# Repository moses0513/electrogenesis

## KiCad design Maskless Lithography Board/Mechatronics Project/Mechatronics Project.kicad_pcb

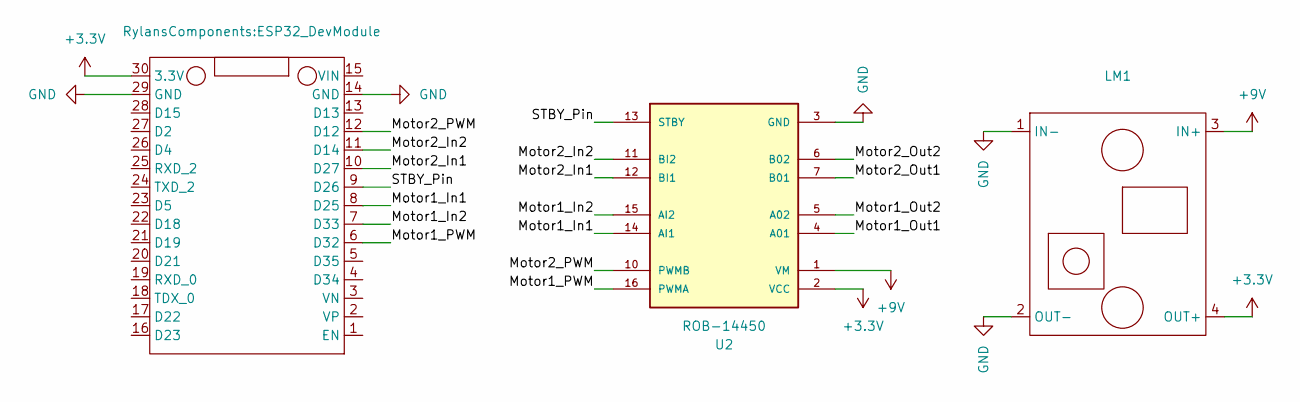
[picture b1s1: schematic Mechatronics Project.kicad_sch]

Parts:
ESP32_DevModule1: ESP32_DevModule
LM1: DC-DC LM2596
U2: ROB-14450; MODULE_ROB-14450; PARTREV 11-13-17

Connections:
+3.3V: ESP32_DevModule1.30 (3.3V), LM1.4 (OUT+), U2.2 (VCC)
+9V: LM1.3 (IN+), U2.1 (VM)
/Motor1_In1: ESP32_DevModule1.8 (D25), U2.14 (AI1)
/Motor1_In2: ESP32_DevModule1.7 (D33), U2.15 (AI2)
/Motor1_Out1: U2.4 (A01)
/Motor1_Out2: U2.5 (A02)
/Motor1_PWM: ESP32_DevModule1.6 (D32), U2.16 (PWMA)
/Motor2_In1: ESP32_DevModule1.10 (D27), U2.12 (BI1)
/Motor2_In2: ESP32_DevModule1.11 (D14), U2.11 (BI2)
/Motor2_Out1: U2.7 (B01)
/Motor2_Out2: U2.6 (B02)
/Motor2_PWM: ESP32_DevModule1.12 (D12), U2.10 (PWMB)
/STBY_Pin: ESP32_DevModule1.9 (D26), U2.13 (STBY)
GND: ESP32_DevModule1.14 (GND), ESP32_DevModule1.29 (GND), LM1.1 (IN-), LM1.2 (OUT-), U2.3 (GND), U2.8 (GND), U2.9 (GND)

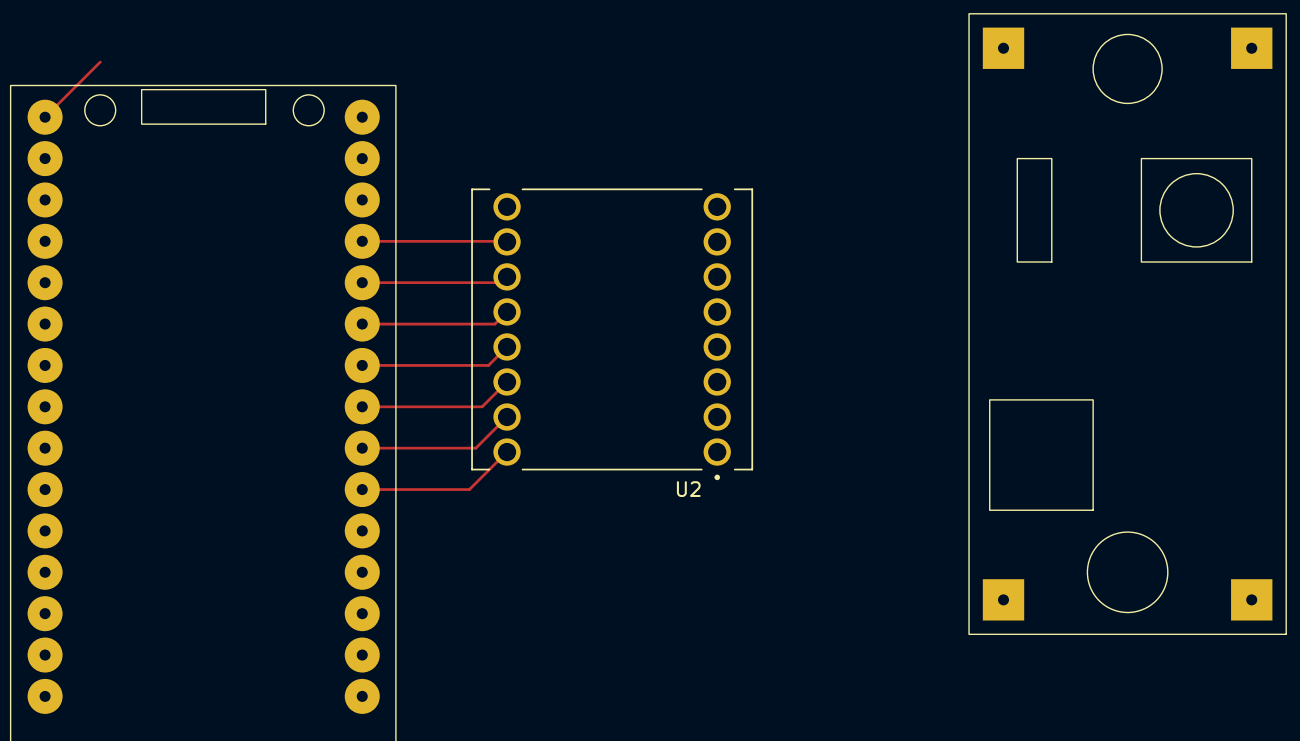
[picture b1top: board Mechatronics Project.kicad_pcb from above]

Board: 2 copper layers, 3 parts (0 on the bottom side), 10 nets.

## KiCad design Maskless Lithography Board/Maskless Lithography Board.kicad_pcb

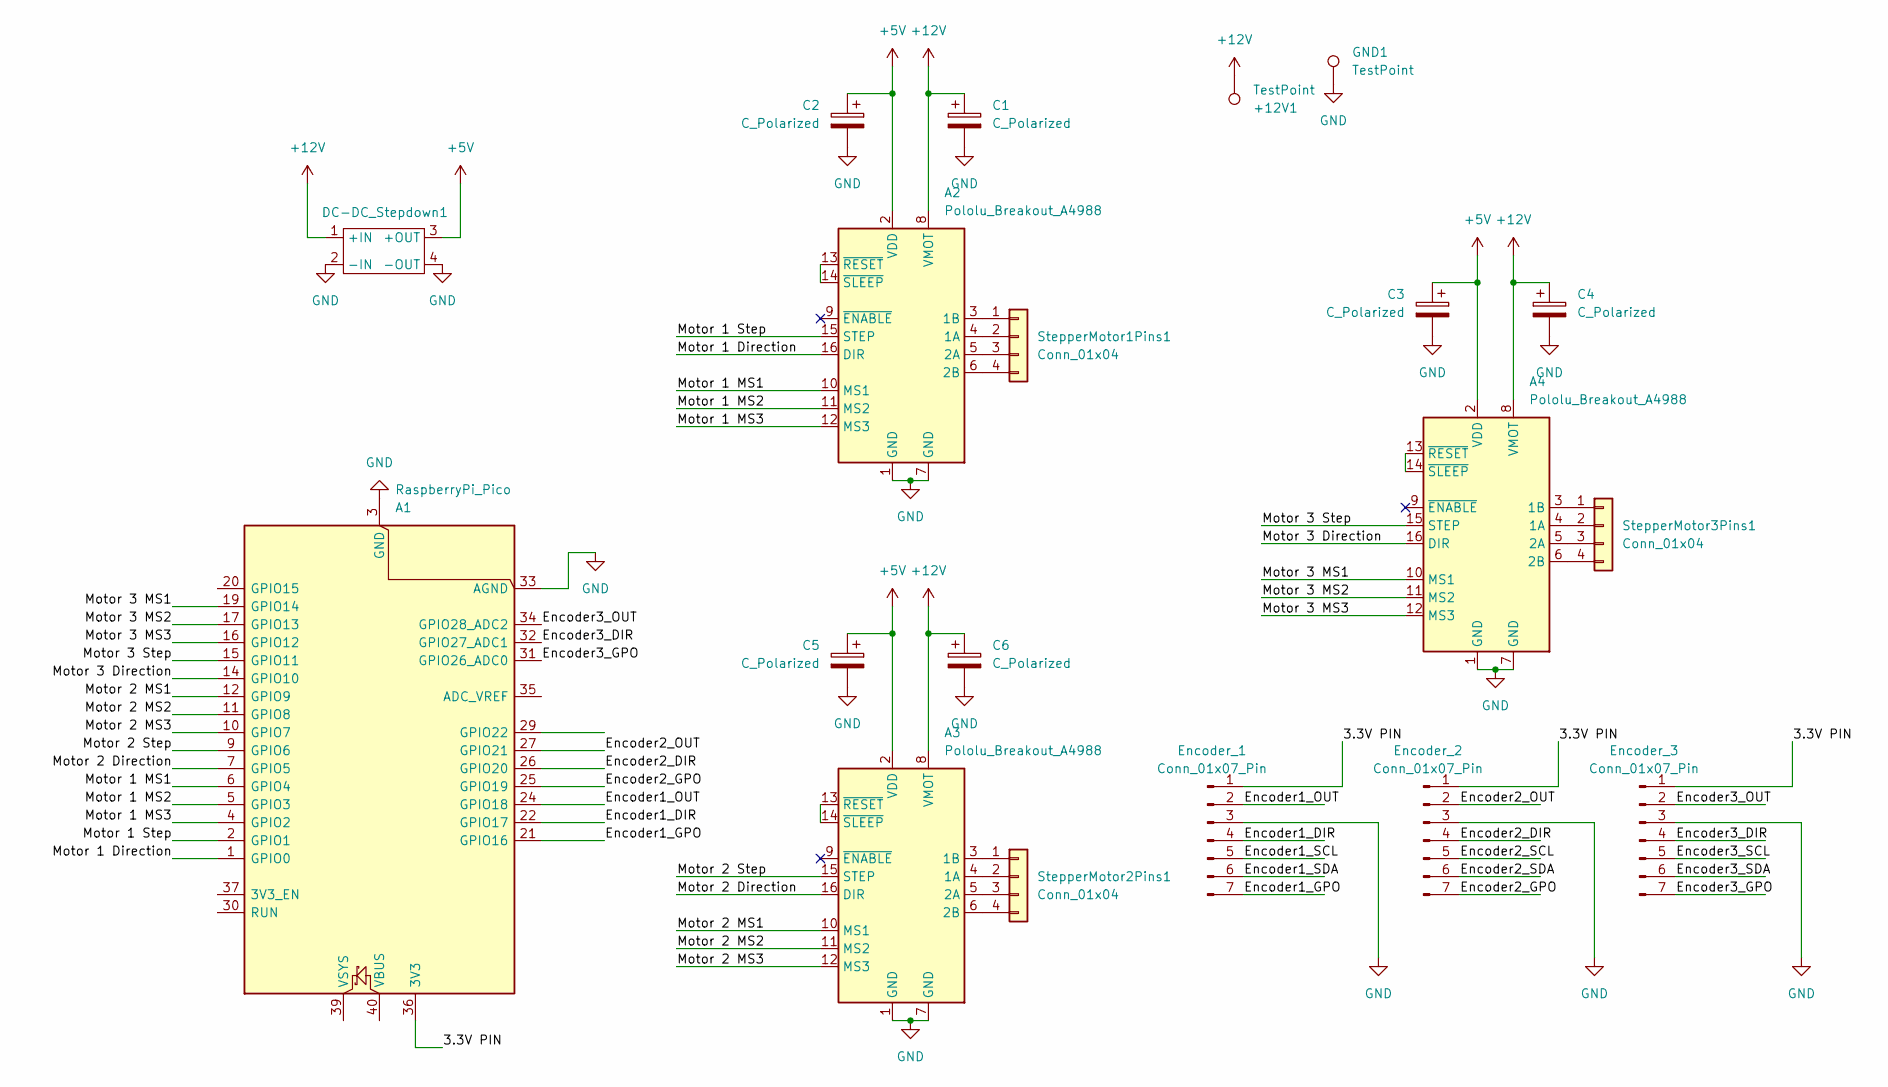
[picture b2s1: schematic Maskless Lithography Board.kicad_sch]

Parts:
+12V1: TestPoint; TestPoint_THTPad_D3.0mm_Drill1.5mm
A1: RaspberryPi_Pico; RaspberryPi_Pico_Common_Unspecified
A2, A3, A4: Pololu_Breakout_A4988; Pololu_Breakout-16_15.2x20.3mm
C1, C4, C6: C_Polarized; CP_Radial_D5.0mm_P2.50mm
C2, C3, C5: C_Polarized; C_Disc_D3.0mm_W1.6mm_P2.50mm
DC-DC_Stepdown1: Mini360_DC-DC_Stepdown
Encoder_1, Encoder_2, Encoder_3: Conn_01x07_Pin; JST_EH_B7B-EH-A_1x07_P2.50mm_Vertical
GND1: TestPoint; TestPoint_THTPad_3.0x3.0mm_Drill1.5mm
StepperMotor1Pins1, StepperMotor2Pins1, StepperMotor3Pins1: Conn_01x04; PinHeader_1x04_P2.54mm_Vertical

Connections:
+5V: A2.2 (VDD), A3.2 (VDD), A4.2 (VDD), C2.1, C3.1, C5.1, DC-DC_Stepdown1.3 (+OUT)
+12V: +12V1.1, A2.8 (VMOT), A3.8 (VMOT), A4.8 (VMOT), C1.1, C4.1, C6.1, DC-DC_Stepdown1.1 (+IN)
/3.3V PIN: A1.36 (3V3), Encoder_1.1, Encoder_2.1, Encoder_3.1
/Encoder1_DIR: A1.22 (GPIO17), Encoder_1.4
/Encoder1_GPO: A1.21 (GPIO16), Encoder_1.7
/Encoder1_OUT: A1.24 (GPIO18), Encoder_1.2
/Encoder1_SCL: Encoder_1.5
/Encoder1_SDA: Encoder_1.6
/Encoder2_DIR: A1.26 (GPIO20), Encoder_2.4
/Encoder2_GPO: A1.25 (GPIO19), Encoder_2.7
/Encoder2_OUT: A1.27 (GPIO21), Encoder_2.2
/Encoder2_SCL: Encoder_2.5
/Encoder2_SDA: Encoder_2.6
/Encoder3_DIR: A1.32 (GPIO27_ADC1), Encoder_3.4
/Encoder3_GPO: A1.31 (GPIO26_ADC0), Encoder_3.7
/Encoder3_OUT: A1.34 (GPIO28_ADC2), Encoder_3.2
/Encoder3_SCL: Encoder_3.5
/Encoder3_SDA: Encoder_3.6
/Motor 1 Direction: A1.1 (GPIO0), A2.16 (DIR)
/Motor 1 MS1: A1.6 (GPIO4), A2.10 (MS1)
/Motor 1 MS2: A1.5 (GPIO3), A2.11 (MS2)
/Motor 1 MS3: A1.4 (GPIO2), A2.12 (MS3)
/Motor 1 Step: A1.2 (GPIO1), A2.15 (STEP)
/Motor 2 Direction: A1.7 (GPIO5), A3.16 (DIR)
/Motor 2 MS1: A1.12 (GPIO9), A3.10 (MS1)
/Motor 2 MS2: A1.11 (GPIO8), A3.11 (MS2)
/Motor 2 MS3: A1.10 (GPIO7), A3.12 (MS3)
/Motor 2 Step: A1.9 (GPIO6), A3.15 (STEP)
/Motor 3 Direction: A1.14 (GPIO10), A4.16 (DIR)
/Motor 3 MS1: A1.19 (GPIO14), A4.10 (MS1)
/Motor 3 MS2: A1.17 (GPIO13), A4.11 (MS2)
/Motor 3 MS3: A1.16 (GPIO12), A4.12 (MS3)
/Motor 3 Step: A1.15 (GPIO11), A4.15 (STEP)
GND: A1.3 (GND), A1.8 (GND), A1.13 (GND), A1.18 (GND), A1.23 (GND), A1.28 (GND), A1.33 (AGND), A1.38 (GND), A2.1 (GND), A2.7 (GND), A3.1 (GND), A3.7 (GND), A4.1 (GND), A4.7 (GND), C1.2, C2.2, C3.2, C4.2, C5.2, C6.2, DC-DC_Stepdown1.2 (-IN), DC-DC_Stepdown1.4 (-OUT), Encoder_1.3, Encoder_2.3, Encoder_3.3, GND1.1
unnamed: A2.4 (1A), StepperMotor1Pins1.2
unnamed: A2.3 (1B), StepperMotor1Pins1.1
unnamed: A2.5 (2A), StepperMotor1Pins1.3
unnamed: A2.6 (2B), StepperMotor1Pins1.4
unnamed: A2.13 (~RESET), A2.14 (~SLEEP)
unnamed: A3.4 (1A), StepperMotor2Pins1.2
unnamed: A3.3 (1B), StepperMotor2Pins1.1
unnamed: A3.5 (2A), StepperMotor2Pins1.3
unnamed: A3.6 (2B), StepperMotor2Pins1.4
unnamed: A3.13 (~RESET), A3.14 (~SLEEP)
unnamed: A4.4 (1A), StepperMotor3Pins1.2
unnamed: A4.3 (1B), StepperMotor3Pins1.1
unnamed: A4.5 (2A), StepperMotor3Pins1.3
unnamed: A4.6 (2B), StepperMotor3Pins1.4
unnamed: A4.13 (~RESET), A4.14 (~SLEEP)

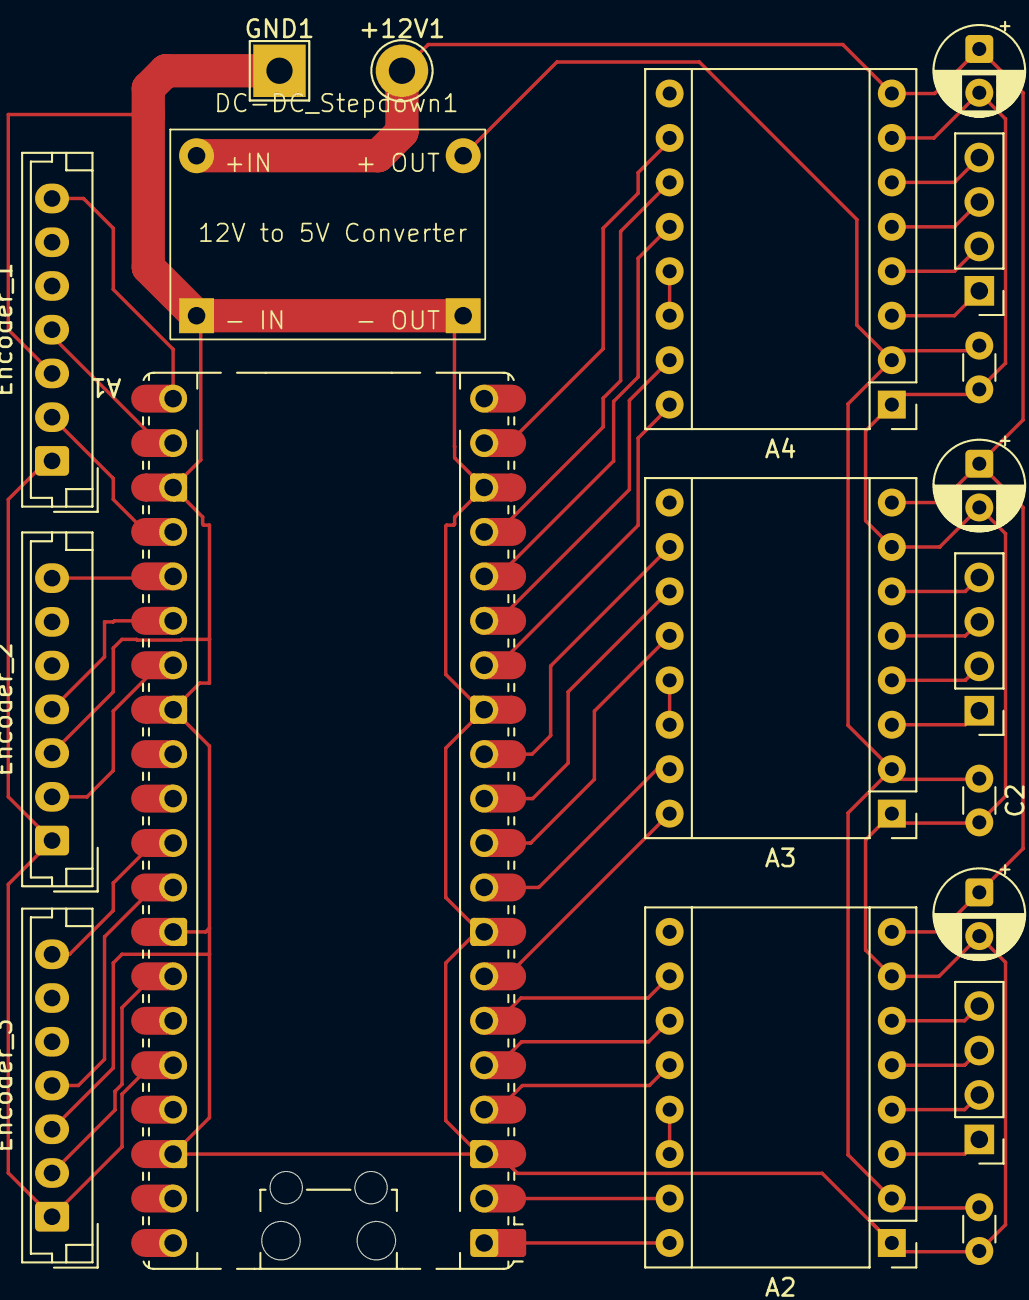
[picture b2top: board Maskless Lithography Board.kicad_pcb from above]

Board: 2 copper layers, 19 parts (0 on the bottom side), 43 nets.

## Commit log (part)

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2025-09-26 Add CODEOWNERS file for review requirements
    Set CODEOWNERS to require reviews from specified users.
2025-09-26 deleted test
2025-09-28 added MicroPython project
2025-09-28 added Hash
2025-09-29 added MotorController class
2025-09-30 I added a comment
2025-10-07 del blink.py
2025-10-07 modified MotorController class
2025-10-14 added PCB folder and edited code
2025-10-19 Adding PCB folder
2025-10-28 software_for_control
2025-10-28 Added logo to controller
2025-10-28 fixed working directory for image
2025-10-28 added keyboard shortcuts
2025-10-28 made .exe file, included keyboard shortcuts, and a .bat file
2025-11-02 Add SVG to HDMI code
2025-11-04 iPad commit test
2025-11-04 Trying Tkinter
2025-11-05 Testing Qt modules
2025-11-05 Basic lithography image program test
2025-11-09 GUI framework for photolithography imaging system
2025-11-10 Updated GUI
2025-11-11 Removed colorize effect, added numpy addition, fixed broken preview
2025-11-11 added magnetic encoder code
2025-11-11 adding ME code to jacob
2026-01-13 i dont know what these are for
2026-01-15 testing changes from micro python to python
2026-01-15 sim in PC works as well
2026-01-15 new changes
2026-01-15 i dont know
2026-01-15 switching to jacob
2026-01-15 del some stuff
2026-01-20 claude changes
2026-01-20 added live camera to GUI
2026-01-22 working on key bindings
2026-01-22 keybind update
2026-01-22 changed back to original pyqt5
2026-01-22 XYZ gantry coordinates display
2026-01-22 changed to original pyqt6
2026-01-26 accidentally coded on main, moved changes to branch \'jacob\'
2026-01-26 pylon
2026-01-29 renamed old GUI folder with PyQt5
2026-01-29 camera update
2026-01-29 blended image
2026-01-29 pypylon qimg
2026-01-31 PyPylon works on RPi now, camera is in GUI.
2026-01-31 added grayscale camera option to fix "rainbow vomit" problem
2026-02-01 GUI working with DLP
2026-02-02 removed 'draw circle' option, connected 'draw alignment' checkbox
2026-02-03 fixes
2026-02-03 successfully changed bars to H
2026-02-03 theading, exposure button
2026-02-03 sliders fixed
2026-02-03 magnetic encoder converted to .py from micropy
2026-02-03 sliders horizontal
2026-02-03 copied moses encoder file
2026-02-05 finished exposure timer, fixed image scaling (preview)
2026-02-07 fixing alignment on camera, added todo.txt
2026-02-18 Converted stage controller to PyQt6
2026-02-18 Repositioned GUI with stage controller
2026-02-18 Positioned stage controller in GUI (2)
2026-02-24 experimental DLP scene fix
2026-02-24 stuff
2026-03-24 stylesheets
2026-03-26 styles
2026-04-11 config updates
2026-04-30 bug fix graphics item not deleting after different exposures
2026-04-30 check
